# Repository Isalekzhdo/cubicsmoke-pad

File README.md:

# cubicsmoke-pad
Hello, this is my first Hackpad

BOM
-5x Cherry MX switches
-1x Xiao Rp2040
-5x DSA keycaps 
-4x M3x16mm screws
-4x M3x5mx4mm heatset inserts
-2x SK6812 MINI-E LEDs
That's lowkey it

This is my hackpad

This is my schematic and PCB

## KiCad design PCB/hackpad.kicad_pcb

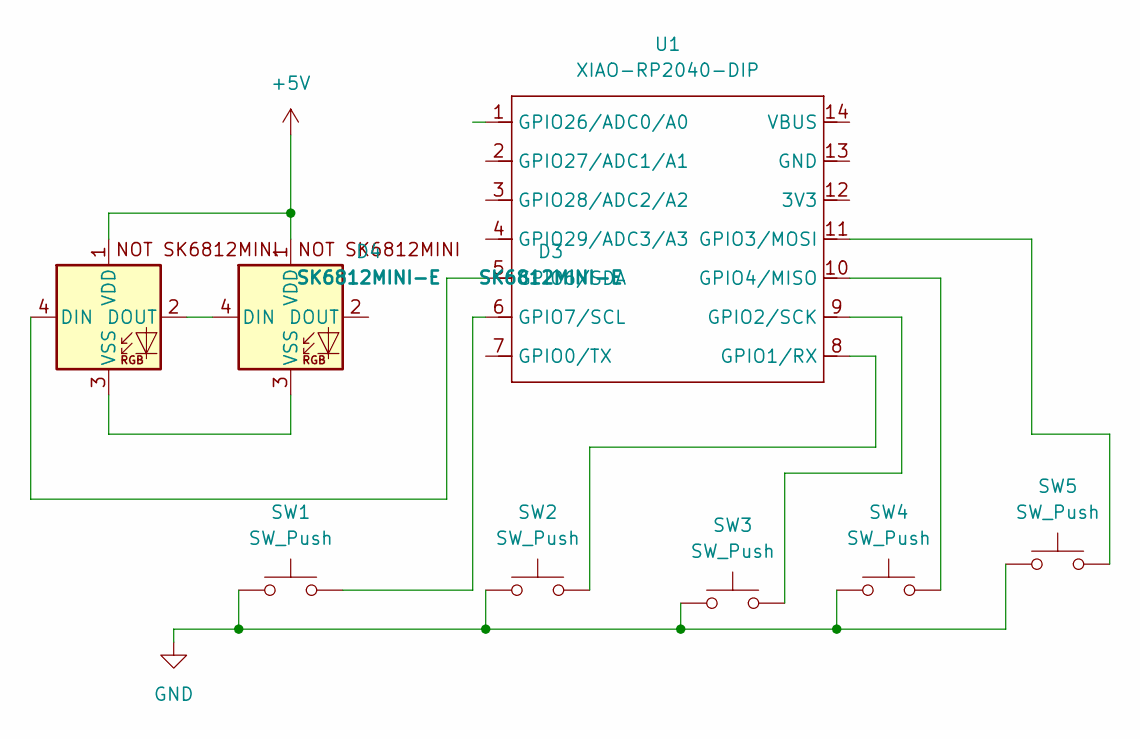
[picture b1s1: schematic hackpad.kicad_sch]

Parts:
D3, D4: SK6812MINI-E; SK6812MINI-E - 3.2x2.8x1.78mm
SW1, SW2, SW3, SW4, SW5: SW_Push; SW_Cherry_MX_1.00u_PCB
U1: XIAO-RP2040-DIP

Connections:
+5V: D3.1 (VDD), D4.1 (VDD)
GND: SW1.1, SW2.1, SW3.1, SW4.1, SW5.1
unnamed: D3.4 (DIN), D4.2 (DOUT)
unnamed: D3.3 (VSS), D4.3 (VSS)
unnamed: D4.4 (DIN), U1.5 (GPIO6/SDA)
unnamed: SW2.2, U1.8 (GPIO1/RX)
unnamed: SW3.2, U1.9 (GPIO2/SCK)
unnamed: SW5.2, U1.11 (GPIO3/MOSI)
unnamed: SW4.2, U1.10 (GPIO4/MISO)
unnamed: SW1.2, U1.6 (GPIO7/SCL)

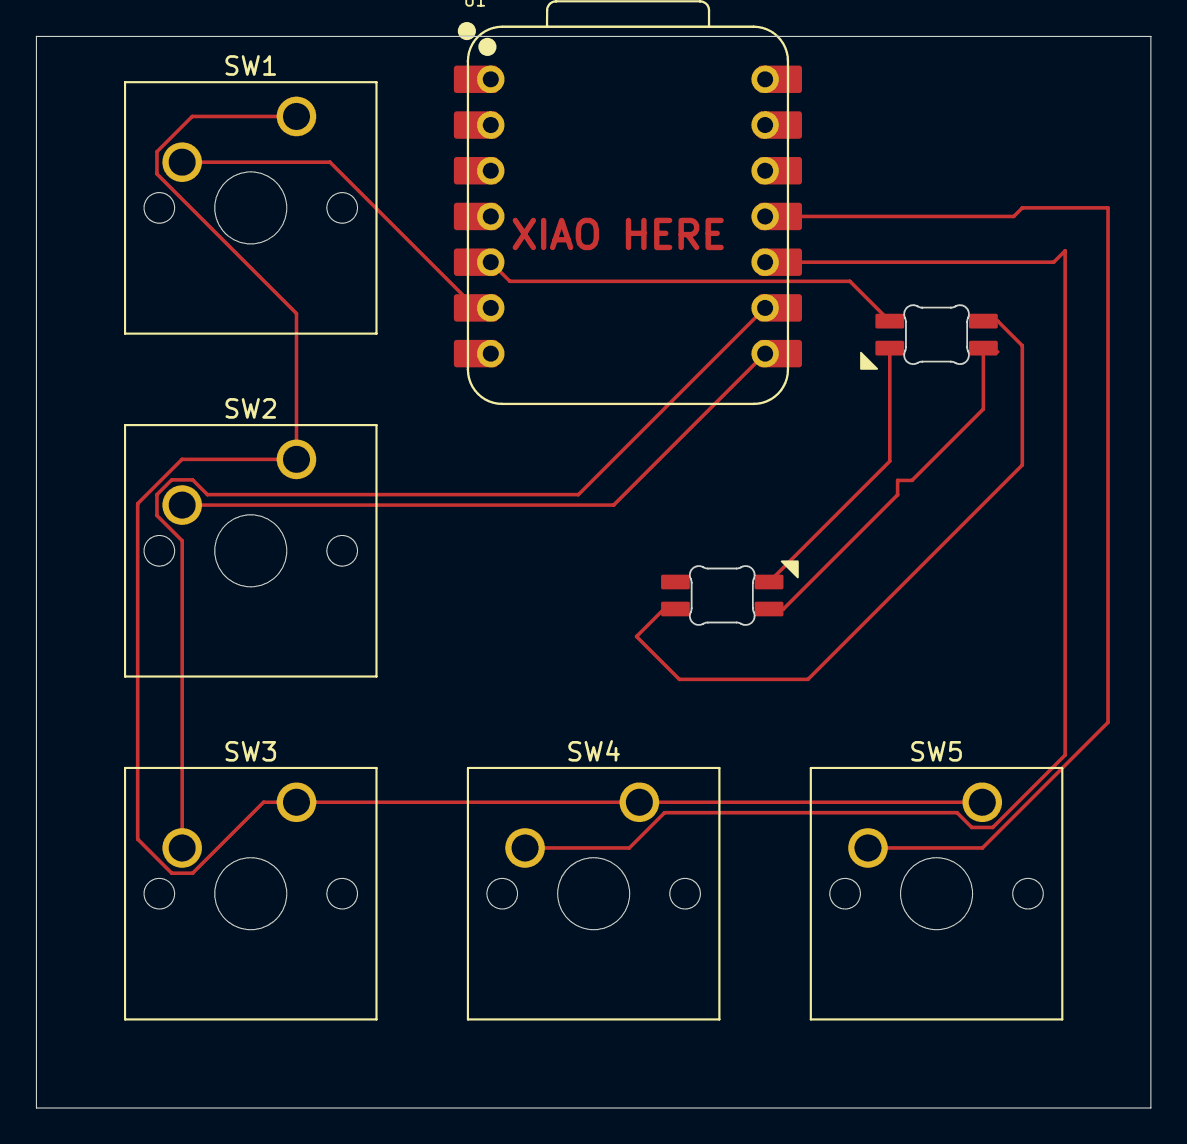
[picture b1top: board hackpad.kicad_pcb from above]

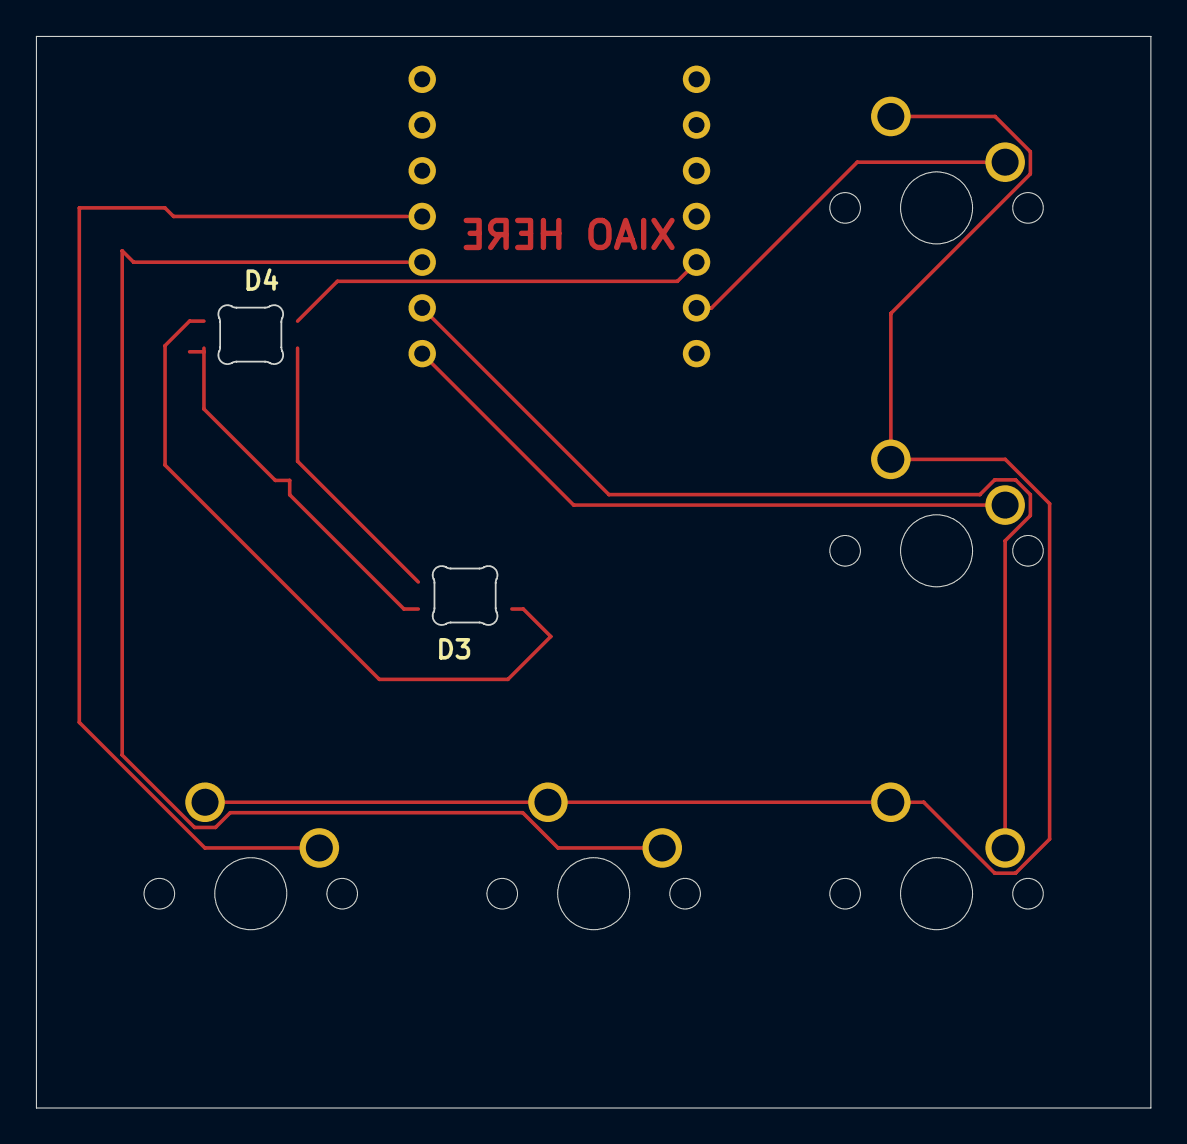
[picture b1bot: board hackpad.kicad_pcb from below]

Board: 2 copper layers, 61.9 x 59.5 mm, 8 parts (2 on the bottom side), 10 nets.

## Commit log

2026-01-27 Add files via upload
    pcb
2026-01-27 Create a
2026-01-27 Add new file CAD/a
2026-01-27 Create l
2026-01-27 Enhance README with project details and images
    Added detailed description and images for the hackpad.
2026-01-27 Revise README formatting and add images
    Updated headings and added images to README.
2026-01-28 Replace old images with new ones in README
